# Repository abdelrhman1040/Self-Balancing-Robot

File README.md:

# Self-Balancing Robot
### Inverted Pendulum Modeling, Embedded Control, and Real-Time PID Tuning Platform

</div>

## Project Overview

This project implements a self-balancing robot based on the classical inverted pendulum problem. The system is inherently unstable and requires continuous feedback control to maintain its upright position.

Distinct from standard implementations, this robot features a **Web-based Dashboard** hosted directly on the ESP32. This allows for **real-time PID tuning** and telemetry visualization over Wi-Fi, eliminating the need to re-upload firmware for parameter adjustments.

### Key Features
* **Mathematical Modeling:** Linearization and transfer function derivation of the system.
* **Control System Design:** Implementation of cascaded PID loops for stability and drift control.
* **Embedded Firmware:** High-frequency control loop execution on the ESP32 dual-core architecture.
* **Web Interface:** Real-time tuning and data plotting using WebSockets.
* **Hardware Implementation:** Custom PCB design and 3D printed mechanical chassis.

### Applications
* Autonomous robotics platforms.
* Mobile balancing transport systems.
* Educational control systems laboratories.
* Real-time embedded control experimentation.

---

## Repository Contents

This repository is organized into the following directories:

* **[`/Firmware`](./Firmware)**: Source code (PlatformIO/Arduino) and libraries.
* **[`/PCB`](./PCB)**: EasyEDA Gerber files, schematics, and BOM.
* **[`/Mechanical`](./Mechanical)**: STL files for 3D printing and CAD models.
* **[`/Hardware`](./Hardware)**: Component datasheets, wiring diagrams, and hardware specifications.

---

## Hardware Assembly

### 1. Mechanical Assembly

1.  **Chassis Fabrication:** 3D print the chassis using the STL files provided in the `/Mechanical` directory.
2.  **Motor Mounting:** Mount the NEMA17 stepper motors in the designated chassis slots.
3.  **Drive Train:** Securely attach the wheels to the motor shafts.
4.  **Electronics Mounting:** Fix the PCB in its mounting slots using M3 screws.
5.  **IMU Alignment:** Place the BNO055 IMU sensor at the physical center of the robot.
    * *Note:* Misalignment introduces centrifugal acceleration artifacts into the tilt reading.
6.  **Center of Mass:** Ensure the center of mass is aligned vertically above the wheel axis.

### 2. Electrical Assembly

Connect the components according to the schematic provided in the `/PCB` directory:

* **Microcontroller:** ESP32 Development Board.
* **Actuators:** Two Stepper Motors driven by A4988 or DRV8825 drivers.
* **Sensor:** BNO055 IMU communicating via I2C (SDA, SCL).
* **Power Management:** Buck converter (16V to 5V) for logic supply; direct battery connection for motor drivers.

**Verification Steps:**
* Calibrate motor driver current limits (Vref).
* Verify common ground continuity between logic and power circuits.
* Ensure I2C connections are secure and shielded.

---

## Firmware Configuration and Upload

To configure and upload the firmware:

1.  Open the project in **PlatformIO** or **Arduino IDE**.
2.  Navigate to the main configuration file (e.g., `config.h` or `main.cpp`).
3.  Update the Wi-Fi credentials:

    ```cpp
    const char* ssid = "your_wifi_name";
    const char* password = "your_wifi_password";
    ```

4.  Upload the firmware to the ESP32.
5.  Open the Serial Monitor (Baud Rate: 115200).
6.  Upon successful connection, the ESP32 will output its assigned IP address.
7.  Enter this IP address in a web browser to access the control dashboard.

---

## Mathematical Modeling

The robot is modeled as an inverted pendulum mounted on a wheeled cart.

```math
(M + m)\ddot{x} + mL \cos\theta \ddot{\theta}
- mL\dot{\theta}^2 \sin\theta = F(x)
```
### 2. Pendulum Rotation

```math
mL \cos\theta \ddot{x}
+ (I + mL^2)\ddot{\theta}
- mgL\sin\theta = d(\theta)
```

These equations contain nonlinear terms:
$\sin\theta$, $\cos\theta$, $\dot{\theta}^2$

For small angles:

$$
\sin\theta \approx \theta
$$

$$
\cos\theta \approx 1
$$

The simplified equation becomes:

$$
(I + mL^2)\ddot{\theta} - mgL\theta = d(\theta)
$$

### Transfer Function

$$
\frac{\Theta(s)}{D(s)} = \frac{1}{s^2 - a}
$$

Where

$$
a = \frac{mgL}{I + mL^2}
$$

Poles:

$$
s = \pm \sqrt{a}
$$

### Embedded Control Architecture

The firmware utilizes a **Cascaded Control Architecture**:

1.  **Balance Loop (Inner Loop):**
    * Operates at high frequency (~200Hz).
    * Calculates motor speed based on tilt angle.
    * Includes anti-windup and deadband compensation.

    ```cpp
    float term_bP = Kp * balanceError;
    float term_bI = Ki * sumBalanceError;
    float term_bD = Kd * (balanceError - lastBalanceError);
    ```

2.  **Speed/Drift Loop (Outer Loop):**
    * Operates at a lower frequency.
    * Adjusts the target angle setpoint to prevent linear drift across the floor.

    ```cpp
    float term_sP = speedOutput * Kp_s;
    float term_sI = sumSpeedError * Ki_s;
    float driftCorrection = term_sP + term_sI;
    ```

---

## Web Dashboard Interface

The ESP32 hosts an asynchronous web server providing a control interface with the following functionalities:

* **Parameter Tuning:** Sliders for adjusting $K_p$, $K_i$, and $K_d$ values for both balance and speed loops instantly.
* **Telemetry:** Live plotting of tilt angle, motor speed, and PID output using Chart.js.
* **Control:** Remote start/stop functionality.
* **Data Persistence:** Capability to save and load tuning profiles from non-volatile memory (EEPROM).

<div align="center">

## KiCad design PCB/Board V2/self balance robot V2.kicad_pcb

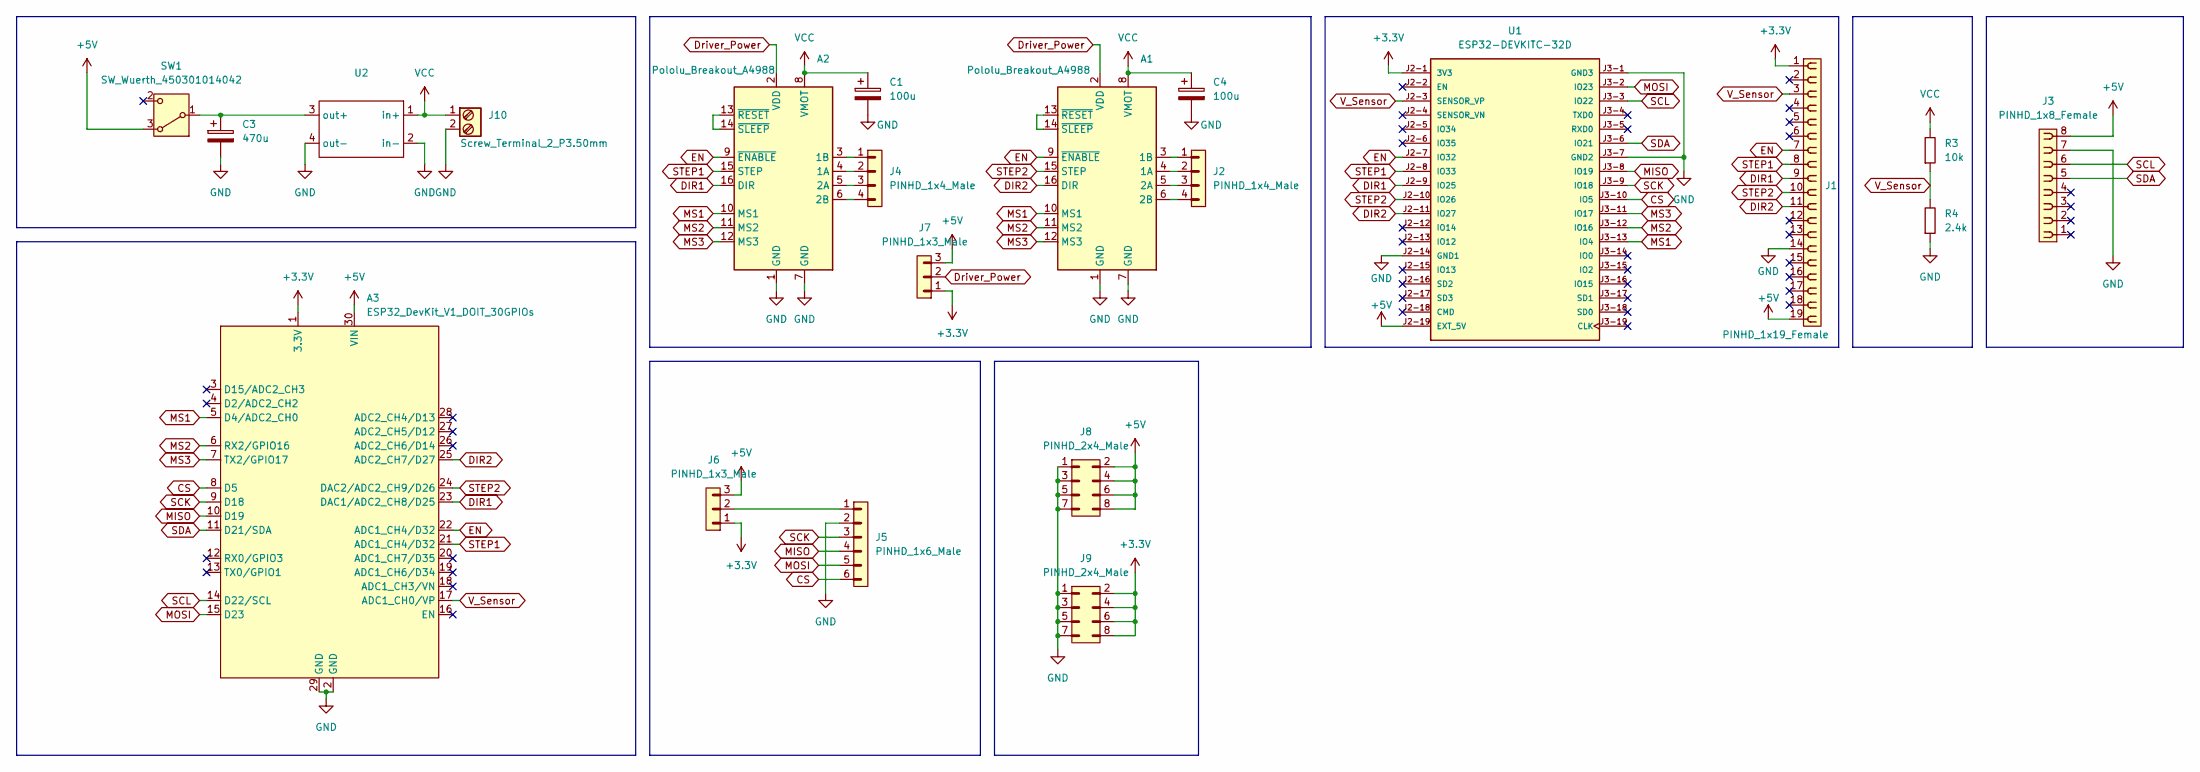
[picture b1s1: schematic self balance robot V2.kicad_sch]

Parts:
A1, A2: Pololu_Breakout_A4988; Pololu_Breakout-16_15.2x20.3mm
A3: ESP32_DevKit_V1_DOIT_30GPIOs; DOIT_ESP32_DEVKIT_30Pins
C1, C4: 100u; CP_Radial_D5.0mm_P2.50mm
C3: 470u; CP_Radial_D5.0mm_P2.50mm
J1: PINHD_1x19_Female; PinSocket_1x19_P2.54mm_Vertical
J2, J4: PINHD_1x4_Male; PinHeader_1x04_P2.54mm_Vertical
J3: PINHD_1x8_Female; PinSocket_1x08_P2.54mm_Vertical
J5: PINHD_1x6_Male; PinHeader_1x06_P2.54mm_Vertical
J6, J7: PINHD_1x3_Male; PinHeader_1x03_P2.54mm_Vertical
J8, J9: PINHD_2x4_Male; PinHeader_2x04_P2.54mm_Vertical
J10: Screw_Terminal_2_P3.50mm; TerminalBlock_Phoenix_PT-1,5-2-3.5-H_1x02_P3.50mm_Horizontal
R3: 10k; R_Axial_DIN0207_L6.3mm_D2.5mm_P10.16mm_Horizontal
R4: 2.4k; R_Axial_DIN0207_L6.3mm_D2.5mm_P10.16mm_Horizontal
SW1: SW_Wuerth_450301014042; SW_Slide-03_Wuerth-WS-SLTV_10x2.5x6.4_P2.54mm
U1: ESP32-DEVKITC-32D; MODULE_ESP32-DEVKITC-32D; PARTREV V4
U2: mini360

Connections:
+3.3V: A3.1 (3.3V), J1.1, J6.1, J7.1, J9.2, J9.4, J9.6, J9.8, U1.J2-1 (3V3)
+5V: A3.30 (VIN), J1.19, J3.8, J6.3, J7.3, J8.2, J8.4, J8.6, J8.8, SW1.3 (A), U1.J2-19 (EXT_5V)
CS: A3.8 (D5), J5.6, U1.J3-10 (IO5)
DIR1: A2.16 (DIR), A3.23 (DAC1/ADC2_CH8/D25), J1.9, U1.J2-9 (IO25)
DIR2: A1.16 (DIR), A3.25 (ADC2_CH7/D27), J1.11, U1.J2-11 (IO27)
Driver_Power: A1.2 (VDD), A2.2 (VDD), J7.2
EN: A1.9 (~ENABLE), A2.9 (~ENABLE), A3.22 (ADC1_CH4/D32), J1.7, U1.J2-7 (IO32)
GND: A1.1 (GND), A1.7 (GND), A2.1 (GND), A2.7 (GND), A3.2 (GND), A3.29 (GND), C1.2, C3.2, C4.2, J1.14, J3.7, J5.2, J8.1, J8.3, J8.5, J8.7, J9.1, J9.3, J9.5, J9.7, J10.2, R4.1, U1.J2-14 (GND1), U1.J3-1 (GND3), U1.J3-7 (GND2), U2.2 (in-), U2.4 (out-)
MISO: A3.10 (D19), J5.4, U1.J3-8 (IO19)
MOSI: A3.15 (D23), J5.5, U1.J3-2 (IO23)
MS1: A1.10 (MS1), A2.10 (MS1), A3.5 (D4/ADC2_CH0), U1.J3-13 (IO4)
MS2: A1.11 (MS2), A2.11 (MS2), A3.6 (RX2/GPIO16), U1.J3-12 (IO16)
MS3: A1.12 (MS3), A2.12 (MS3), A3.7 (TX2/GPIO17), U1.J3-11 (IO17)
unnamed: A1.4 (1A), J2.2
unnamed: A1.3 (1B), J2.1
unnamed: A1.5 (2A), J2.3
unnamed: A1.6 (2B), J2.4
unnamed: A1.13 (~RESET), A1.14 (~SLEEP)
unnamed: A2.4 (1A), J4.2
unnamed: A2.3 (1B), J4.1
unnamed: A2.5 (2A), J4.3
unnamed: A2.6 (2B), J4.4
unnamed: A2.13 (~RESET), A2.14 (~SLEEP)
unnamed: J5.1, J6.2
unnamed: C3.1, SW1.1 (B), U2.3 (out+)
SCK: A3.9 (D18), J5.3, U1.J3-9 (IO18)
SCL: A3.14 (D22/SCL), J3.6, U1.J3-3 (IO22)
SDA: A3.11 (D21/SDA), J3.5, U1.J3-6 (IO21)
STEP1: A2.15 (STEP), A3.21 (ADC1_CH4/D32), J1.8, U1.J2-8 (IO33)
STEP2: A1.15 (STEP), A3.24 (DAC2/ADC2_CH9/D26), J1.10, U1.J2-10 (IO26)
VCC: A1.8 (VMOT), A2.8 (VMOT), C1.1, C4.1, J10.1, R3.2, U2.1 (in+)
V_Sensor: A3.17 (ADC1_CH0/VP), J1.3, R3.1, R4.2, U1.J2-3 (SENSOR_VP)

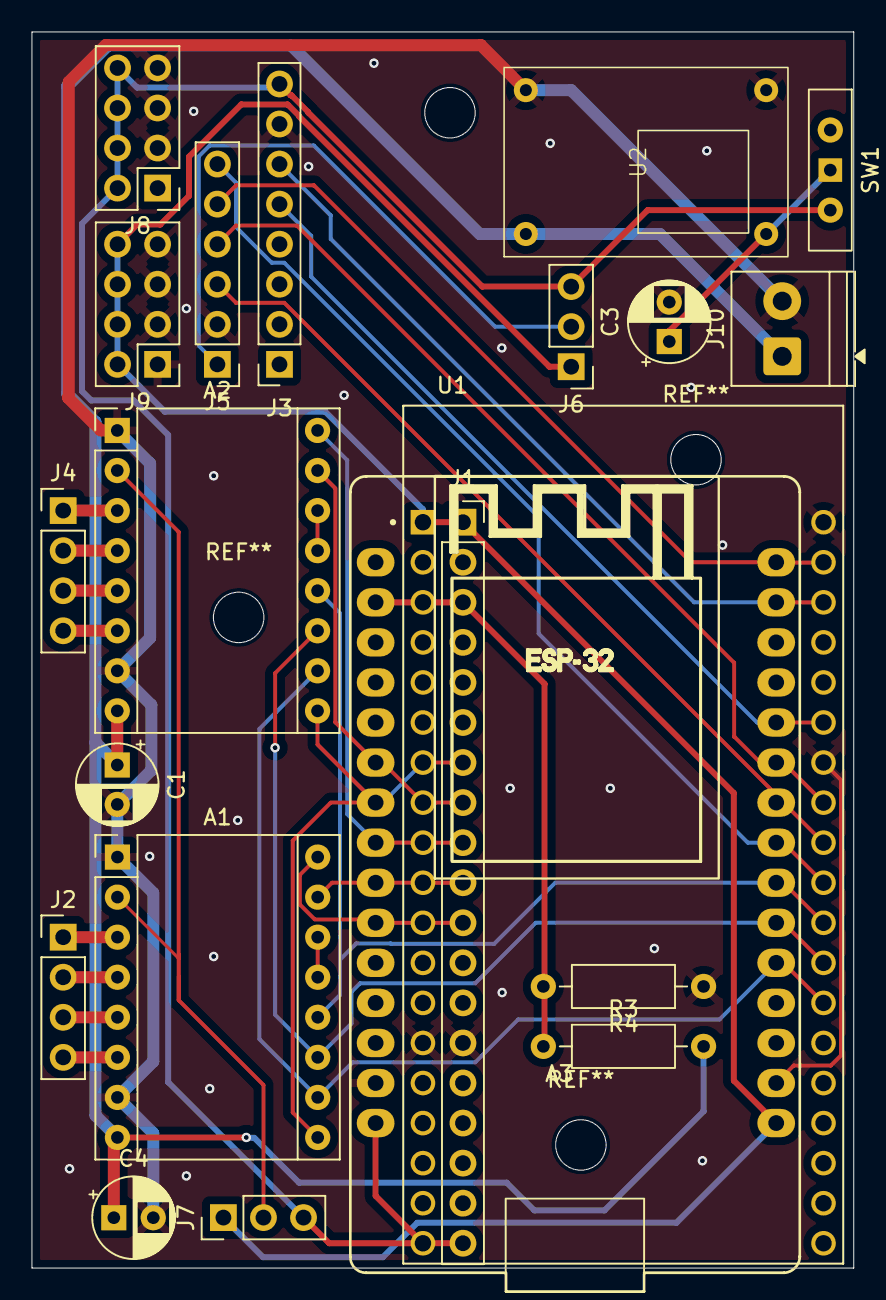
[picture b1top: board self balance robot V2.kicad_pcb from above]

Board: 2 copper layers, 52.1 x 78.4 mm, 21 parts (0 on the bottom side), 32 nets.

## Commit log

2026-02-01 Rename project from 'Self-Balancing-Robot' to 'PCB V1'
2026-02-01 Add images to PCB V1 README
    Added images to the README for better visualization.
2026-02-01 Update images in README for PCB V1
2026-02-03 Update README with PCB version specifications
    Added detailed specifications and improvements for PCB versions 1 and 2, including power management and compatibility notes.
2026-02-03 Update important notes for PCB design V2
2026-02-13 Revise README for clarity and detail
    Updated project title and expanded README with detailed sections on project overview, assembly instructions, mathematical modeling, control strategy, and repository contents.
2026-02-13 Add image to Firmware README
    Added image to README for better visualization.
2026-02-13 Update equation for system stability in README
    Clarified the equation for the system's poles.
